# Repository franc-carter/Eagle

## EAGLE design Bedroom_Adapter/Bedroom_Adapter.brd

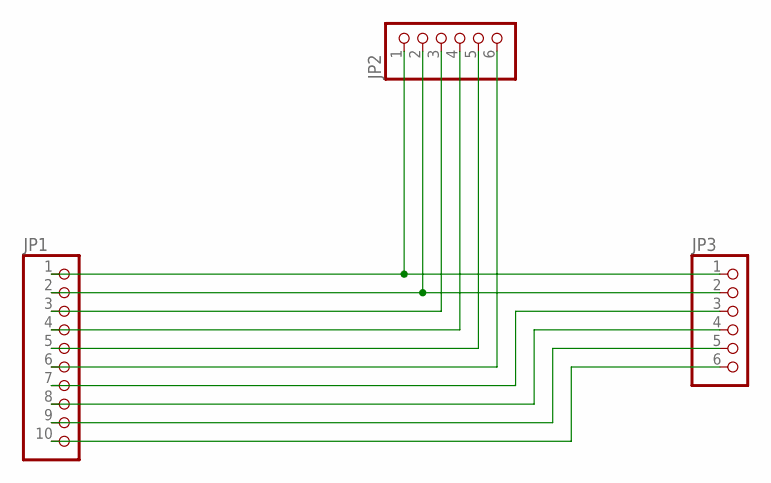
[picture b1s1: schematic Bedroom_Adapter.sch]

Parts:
JP1: PINHD-1X10; 1X10
JP2, JP3: PINHD-1X6; 1X06

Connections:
unnamed: JP1.1, JP2.1, JP3.1
unnamed: JP1.2, JP2.2, JP3.2
unnamed: JP1.3, JP2.3
unnamed: JP1.4, JP2.4
unnamed: JP1.5, JP2.5
unnamed: JP1.6, JP2.6
unnamed: JP1.7, JP3.3
unnamed: JP1.8, JP3.4
unnamed: JP1.9, JP3.5
unnamed: JP1.10, JP3.6

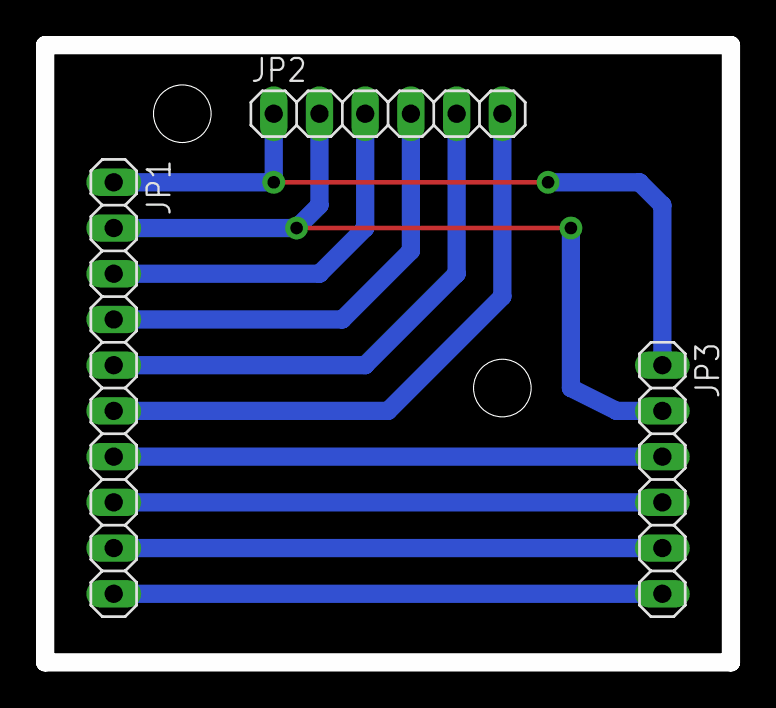
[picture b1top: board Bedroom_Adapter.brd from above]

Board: 2 copper layers, 38.1 x 34.3 mm, 3 parts (0 on the bottom side), 10 nets.

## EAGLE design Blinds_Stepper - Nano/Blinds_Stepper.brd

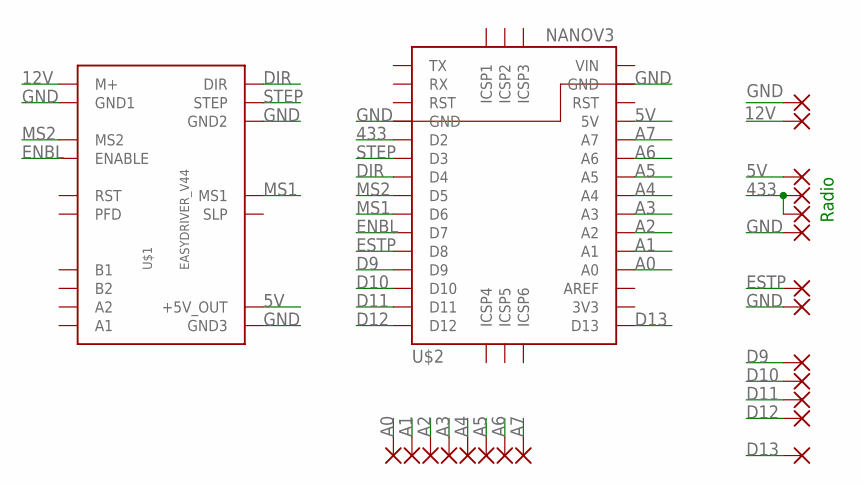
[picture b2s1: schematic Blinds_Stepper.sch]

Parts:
+12: 1,6/0,8
A0, A1, A2, A3, A4, A5, A6, A7: 1,6/0,8
D1, D9, D10, D11, D12: 1,6/0,8
END+: 1,6/0,8
END-: 1,6/0,8
GND: 1,6/0,8
R1, R2: 1,6/0,8
R+: 1,6/0,8
R-: 1,6/0,8
U$1: EASYDRIVER_V44
U$2: NANOV3

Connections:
5V: R+.1, U$1.P$11 (+5V_OUT), U$2.5V
12V: +12.1, U$1.M+
433: R1.1, R2.1, U$2.D2
A0: A0.1, U$2.A0
A1: A1.1, U$2.A1
A2: A2.1, U$2.A2
A3: A3.1, U$2.A3
A4: A4.1, U$2.A4
A5: A5.1, U$2.A5
A6: A6.1, U$2.A6
A7: A7.1, U$2.A7
D9: D9.1, U$2.D9
D10: D10.1, U$2.D10
D11: D11.1, U$2.D11
D12: D12.1, U$2.D12
D13: D1.1, U$2.D13
DIR: U$1.DIR, U$2.D4
ENBL: U$1.ENABLE, U$2.D7
ESTP: END+.1, U$2.D8
GND: END-.1, GND.1, R-.1, U$1.GND1, U$1.GND2, U$1.GND3, U$2.GND1 (GND), U$2.GND2 (GND)
MS1: U$1.MS1, U$2.D6
MS2: U$1.MS2, U$2.D5
STEP: U$1.STEP, U$2.D3
VIN: U$2.VIN

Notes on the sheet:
Radio

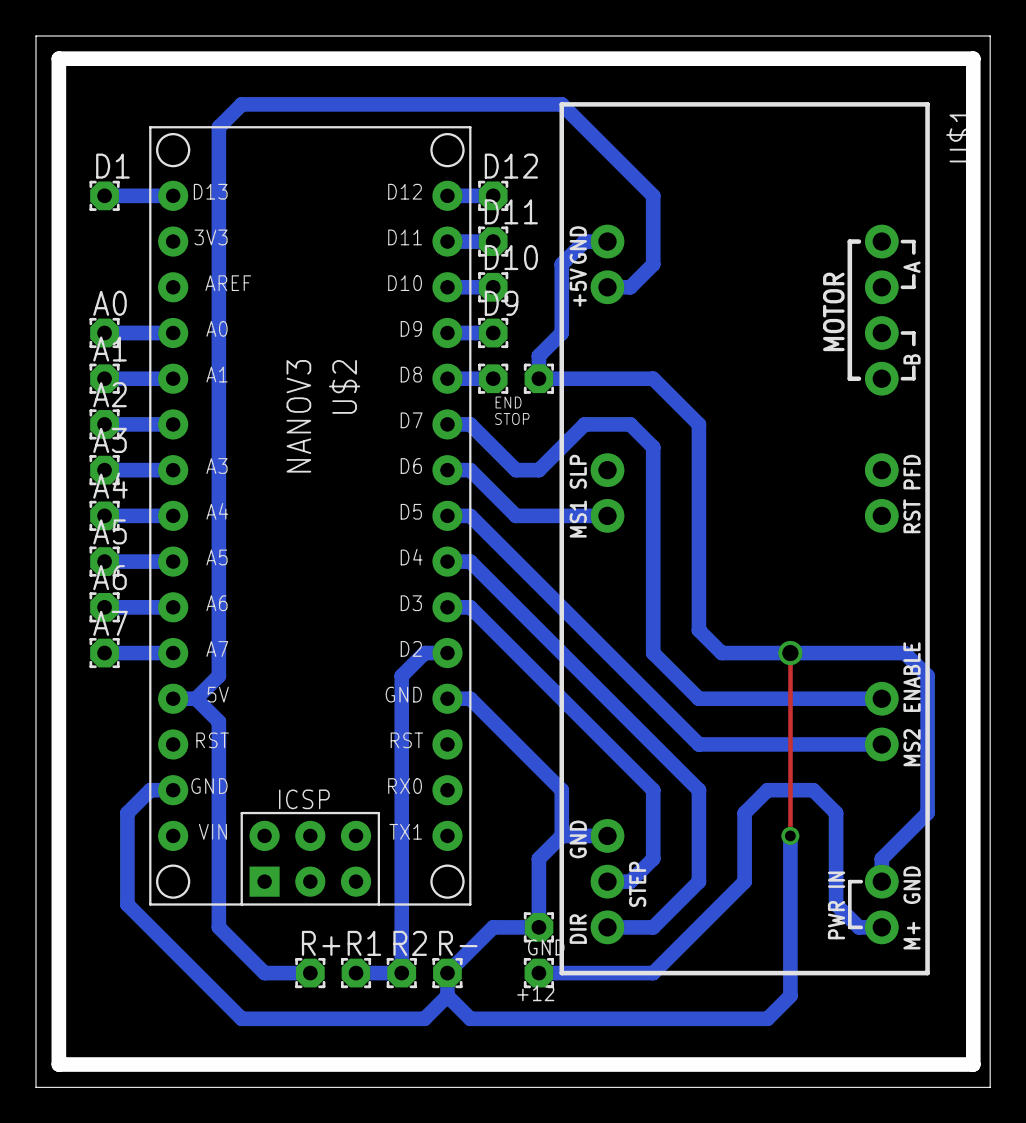
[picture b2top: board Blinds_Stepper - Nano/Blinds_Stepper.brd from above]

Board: 2 copper layers, 53.0 x 58.4 mm, 23 parts (0 on the bottom side), 23 nets.

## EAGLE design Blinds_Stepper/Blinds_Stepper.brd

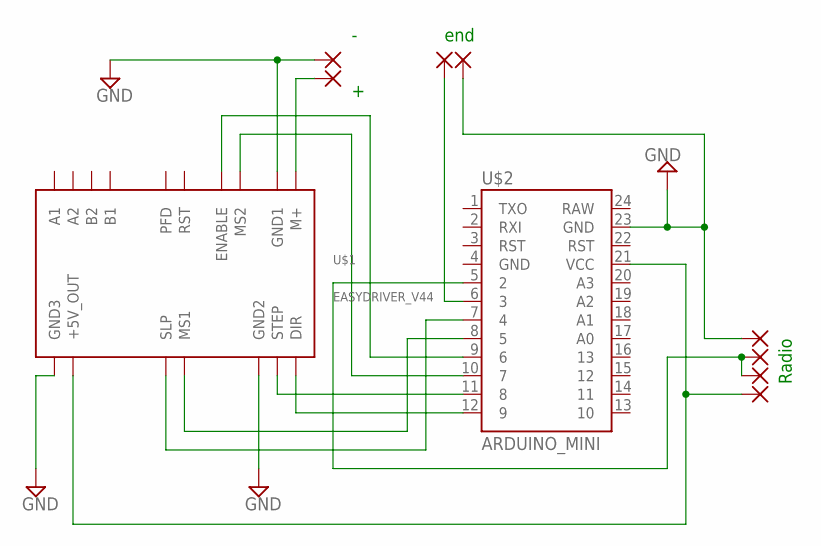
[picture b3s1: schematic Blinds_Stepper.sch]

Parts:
E1, E2: 1,6/0,8
M-: 1,6/0,8
R1, R2: 1,6/0,8
R+: 1,6/0,8
R-: 1,6/0,8
U$1: EASYDRIVER_V44
U$2: ARDUINO_MINI
X: 1,6/0,8

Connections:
GND: E2.1, M-.1, R-.1, U$1.GND1, U$1.GND2, U$1.GND3, U$2.23 (GND)
unnamed: U$1.M+, X.1
unnamed: U$1.DIR, U$2.12 (9)
unnamed: U$1.STEP, U$2.11 (8)
unnamed: U$1.ENABLE, U$2.9 (6)
unnamed: U$1.MS2, U$2.10 (7)
unnamed: U$1.MS1, U$2.8 (5)
unnamed: R+.1, U$1.P$11 (+5V_OUT), U$2.21 (VCC)
unnamed: E1.1, U$2.6 (3)
unnamed: R1.1, R2.1, U$2.5 (2)
unnamed: U$1.SLEEP (SLP), U$2.7 (4)

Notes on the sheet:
Radio
end

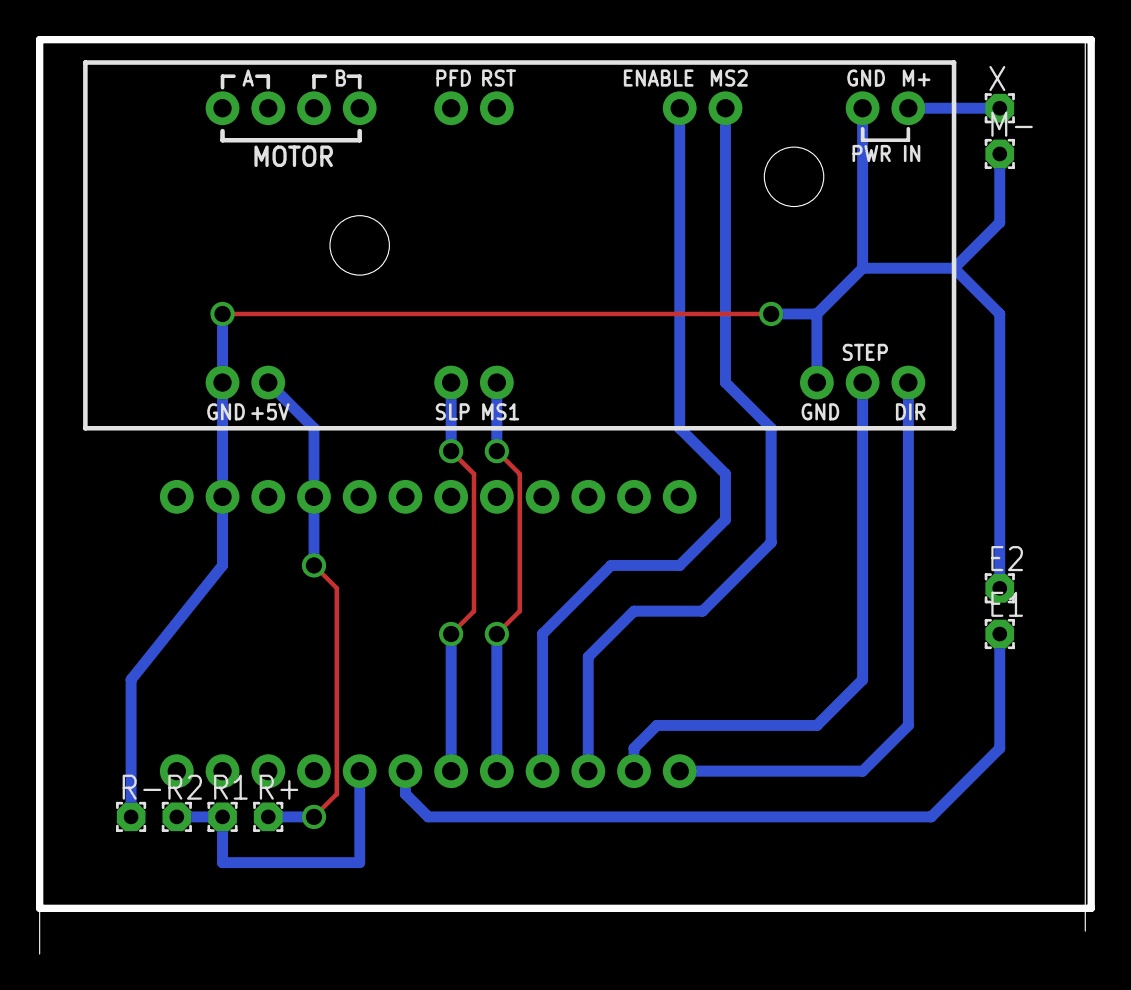
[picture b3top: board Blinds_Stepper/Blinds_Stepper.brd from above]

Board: 2 copper layers, 58.4 x 50.8 mm, 10 parts (0 on the bottom side), 11 nets.

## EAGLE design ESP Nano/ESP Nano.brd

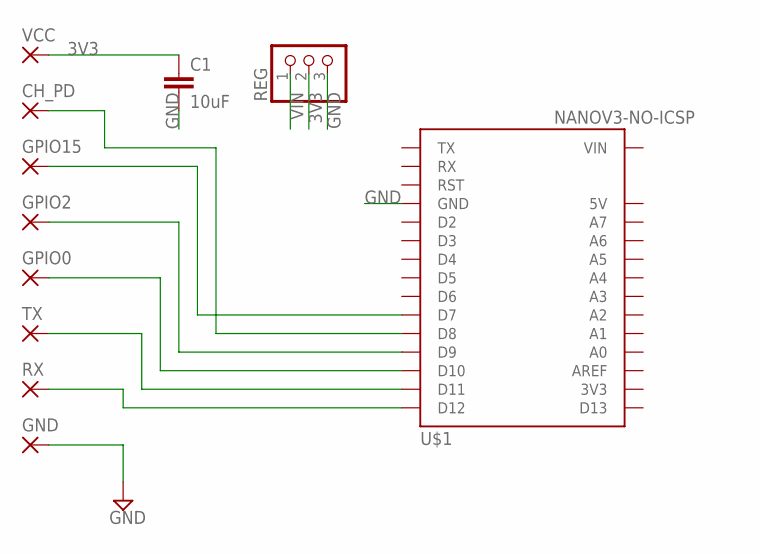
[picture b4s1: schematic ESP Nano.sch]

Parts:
C1: 10uF; C2.5-3
CH_PD: 1,6/0,9
GND: 1,6/0,9
GPIO0, GPIO2, GPIO15: 1,6/0,9
REG: PINHD-1X3; 1X03
RX: 1,6/0,9
TX: 1,6/0,9
U$1: NANOV3-NO-ICSP
VCC: 1,6/0,9

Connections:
3V3: C1.1, REG.2, VCC.1
GND: C1.2, GND.1, REG.3, U$1.GND@1 (GND), U$1.GND@2 (GND)
unnamed: RX.1, U$1.D12
unnamed: GPIO0.1, U$1.D10
unnamed: GPIO2.1, U$1.D9
unnamed: TX.1, U$1.D11
unnamed: GPIO15.1, U$1.D7
unnamed: CH_PD.1, U$1.D8
VIN: REG.1, U$1.VIN

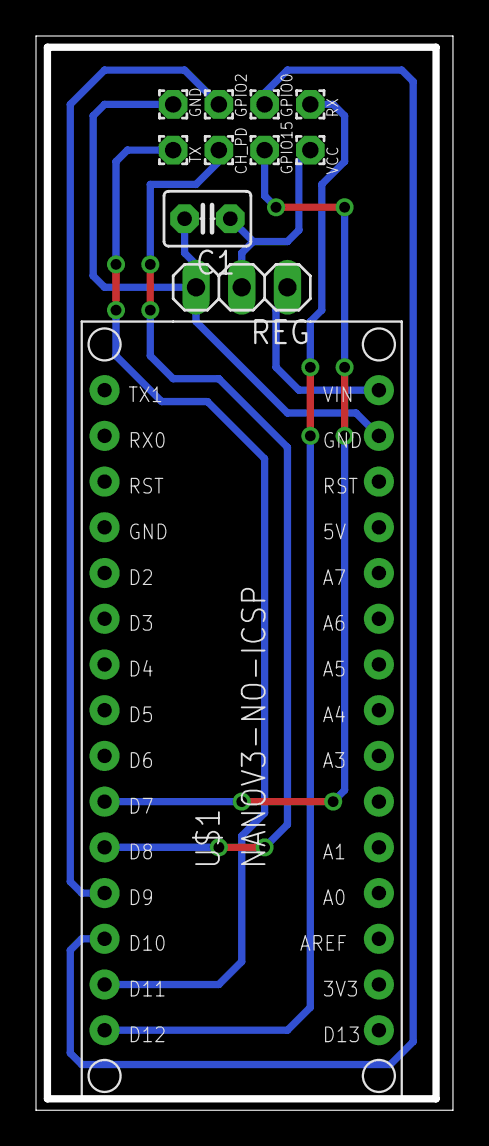
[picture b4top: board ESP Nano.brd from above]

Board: 2 copper layers, 23.2 x 59.7 mm, 11 parts (0 on the bottom side), 9 nets.

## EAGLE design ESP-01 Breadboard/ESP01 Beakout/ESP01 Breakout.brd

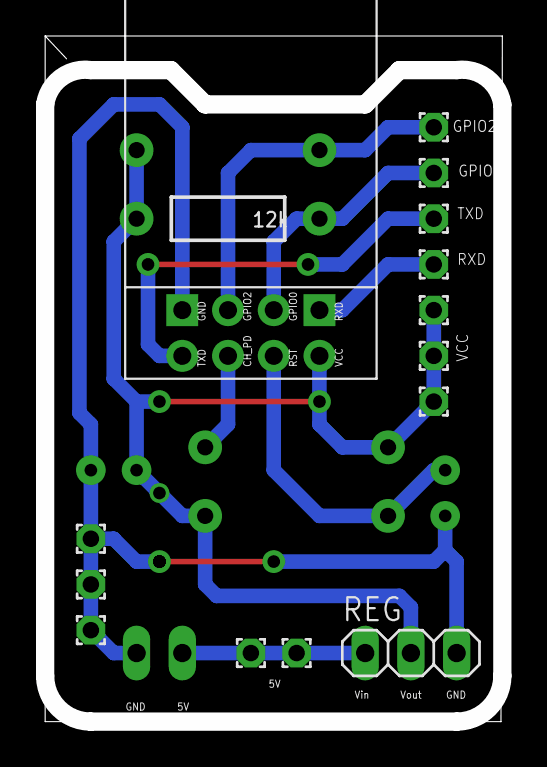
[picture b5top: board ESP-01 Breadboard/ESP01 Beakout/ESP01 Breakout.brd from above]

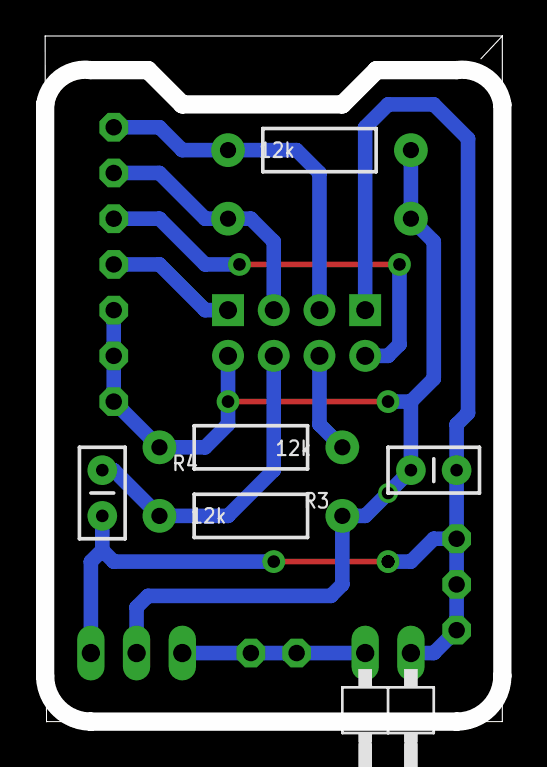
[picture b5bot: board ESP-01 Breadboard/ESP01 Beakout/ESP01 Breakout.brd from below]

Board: 2 copper layers, 25.4 x 38.1 mm, 21 parts (6 on the bottom side), 9 nets.

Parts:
C1: 470pF; CAP-PTH-SMALLEZ
C2: 1uF; CAP-PTH-SMALLEZ
GPIO0, GPIO1, GPIO2, GPIO3, GPIO4, GPIO5, GPIO6, GPIO7, GPIO8, GPIO9, GPIO10: 1,6/0,9
JP2: 1X02/90
R1, R2, R3, R4: 12k; AXIAL-0.4
REG: 1X03
RXD: RXD; 1,6/0,9
U$2: ESP-01

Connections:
3V3: C2.1, GPIO6.1, GPIO7.1, GPIO8.1, R1.P$2, R2.P$2, R3.P$2, R4.P$2, REG.2, U$2.VCC
5V: GPIO9.1, GPIO10.1, JP2.2, REG.1
GND: C1.2, C2.2, GPIO1.1, GPIO4.1, GPIO5.1, JP2.1, REG.3, U$2.GND
GPIO0: GPIO0.1, R1.P$1, U$2.GPIO0
GPIO2: GPIO2.1, R2.P$1, U$2.GPIO2
unnamed: R3.P$1, U$2.CH_PD
REST: C1.1, R4.P$1, U$2.RST
RXD: RXD.1, U$2.RXD
TXD: GPIO3.1, U$2.TXD

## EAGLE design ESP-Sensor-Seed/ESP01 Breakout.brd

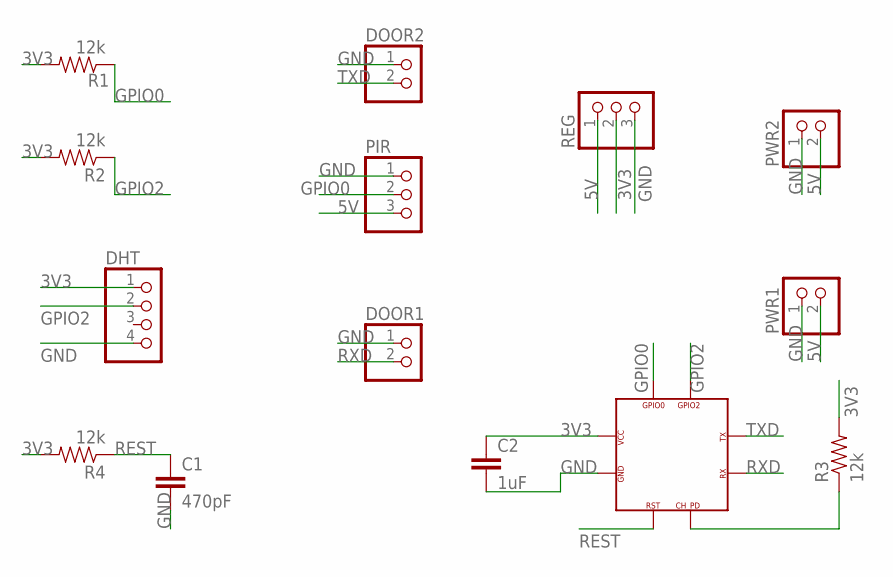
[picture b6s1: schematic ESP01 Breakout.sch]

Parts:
C1: 470pF; CAP-PTH-SMALLEZ
C2: 1uF; CAP-PTH-SMALLEZ
DHT: PINHD-1X4; 1X04
DOOR1, DOOR2: PINHD-1X2/90; 1X02/90
PIR: PINHD-1X3; 1X03
PWR1, PWR2: PINHD-1X2/90; 1X02/90
R1, R2, R3, R4: 12k; AXIAL-0.4
REG: PINHD-1X3; 1X03
U$2: ESP-01

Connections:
3V3: C2.1, DHT.1, R1.P$2 (2), R2.P$2 (2), R3.P$2 (2), R4.P$2 (2), REG.2, U$2.VCC
5V: PIR.3, PWR1.2, PWR2.2, REG.1
GND: C1.2, C2.2, DHT.4, DOOR1.1, DOOR2.1, PIR.1, PWR1.1, PWR2.1, REG.3, U$2.GND
GPIO0: PIR.2, R1.P$1 (1), U$2.GPIO0
GPIO2: DHT.2, R2.P$1 (1), U$2.GPIO2
unnamed: R3.P$1 (1), U$2.CH_PD (CP_PD)
REST: C1.1, R4.P$1 (1), U$2.RST
RXD: DOOR1.2, U$2.RXD (RX)
TXD: DOOR2.2, U$2.TXD (TX)

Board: 2 copper layers, 14 parts (1 on the bottom side), 9 nets, no tracks yet.

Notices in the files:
parts and their libraries:
SparkFun-Boards: Licensing: Creative Commons ShareAlike 4.0 International - https://creativecommons.org/licenses/by-sa/4.0
